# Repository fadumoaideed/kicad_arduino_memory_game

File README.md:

PCB still in progress

Circuit schematics

<br>

PCB

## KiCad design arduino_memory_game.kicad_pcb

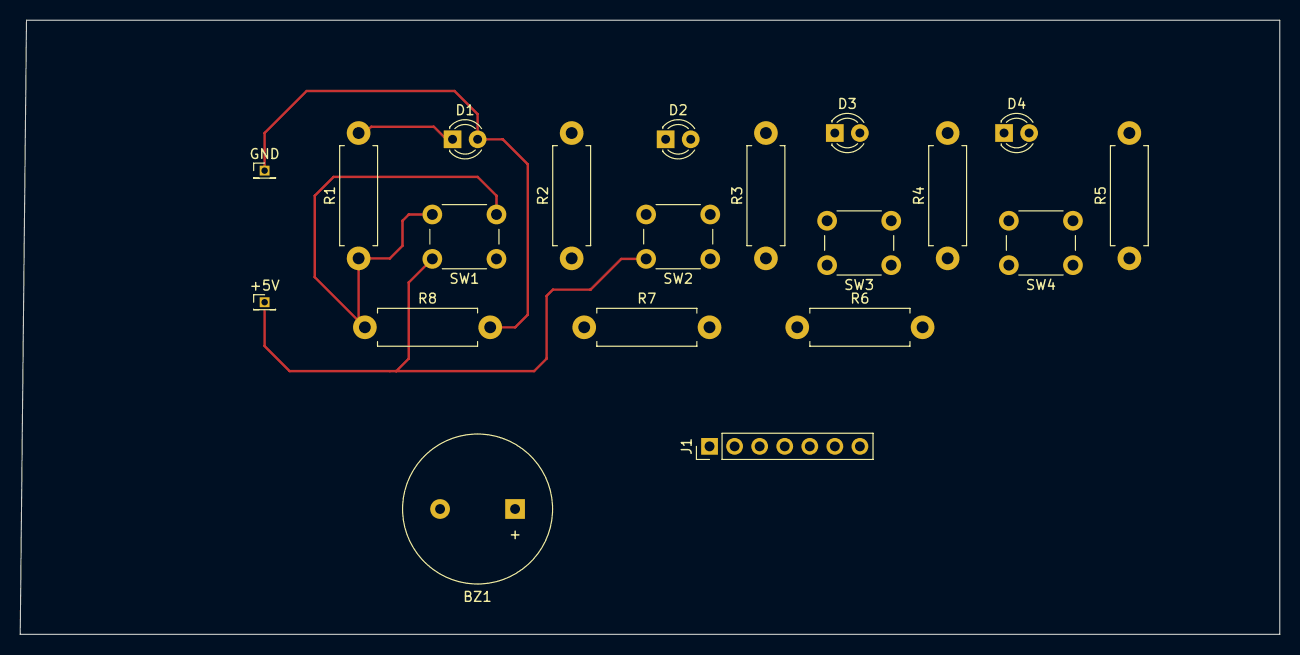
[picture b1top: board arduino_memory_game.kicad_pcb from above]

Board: 2 copper layers, 127.6 x 62.2 mm, 20 parts (0 on the bottom side), 11 nets.

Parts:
+5V: PinHeader_1x01_P1.27mm_Vertical
BZ1: Buzzer; Buzzer_15x7.5RM7.6
D1, D2, D3, D4: LED; LED_D3.0mm
GND: PinHeader_1x01_P1.27mm_Vertical
J1: Conn_01x05; PinHeader_1x07_P2.54mm_Vertical
R1, R2, R3, R4: 330; R_Axial_DIN0411_L9.9mm_D3.6mm_P12.70mm_Horizontal
R5, R6, R7, R8: 1k; R_Axial_DIN0411_L9.9mm_D3.6mm_P12.70mm_Horizontal
SW1, SW2, SW3, SW4: SW_Push; SW_PUSH_6mm

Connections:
2: J1.5, R4.1, R5.1, SW4.2
5: BZ1.1 (-), J1.4
8: J1.3, R3.1, R6.1, SW3.2
10: J1.2, R2.1, R7.1, SW2.2
13: J1.1, R1.1, R8.1, SW1.2
+5V: SW1.1, SW2.1, SW3.1, SW4.1
Earth: BZ1.2 (+), D1.2 (A), D2.2 (A), D3.2 (A), D4.2 (A), GND.1, R5.2, R6.2, R7.2, R8.2
unnamed: D1.1 (K), R1.2
unnamed: D2.1 (K), R2.2
unnamed: D3.1 (K), R3.2
unnamed: D4.1 (K), R4.2

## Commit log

2024-02-05 kicad schematics. TODO pcb design
2024-04-16 update version
